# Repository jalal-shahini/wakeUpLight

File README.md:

# Wake up light

This is the circuit and code for a smart, super bight light that slowly brightens in the mornings to wake me up without an alarm.
The light can also be used as reading light at night with a timer to turn off automatically.
It features a 2004 LCD and a rotary encoder for user input.
The encoder has a calibrated debounce circuit and a schmitt-trigger for the cleanest possible signal.

An LED driver is required alongside this circuit.
I have decided to use a ZK-SJ20 to protect the LED from over current.
Max. LED power is 50 watts.
A CR2032 battery is required for the RTC to keep the time when the power is disconnected.

## To Do

* Since the device is connected to the wall outlet, energy efficiency was not of the highest concern. However, in feauture iterations, I will replace the linear voltage regulator with a buck converter.

**Disclaimer: The design is not yet ready for production. Therefore, the bom and positions files are not accurate.**

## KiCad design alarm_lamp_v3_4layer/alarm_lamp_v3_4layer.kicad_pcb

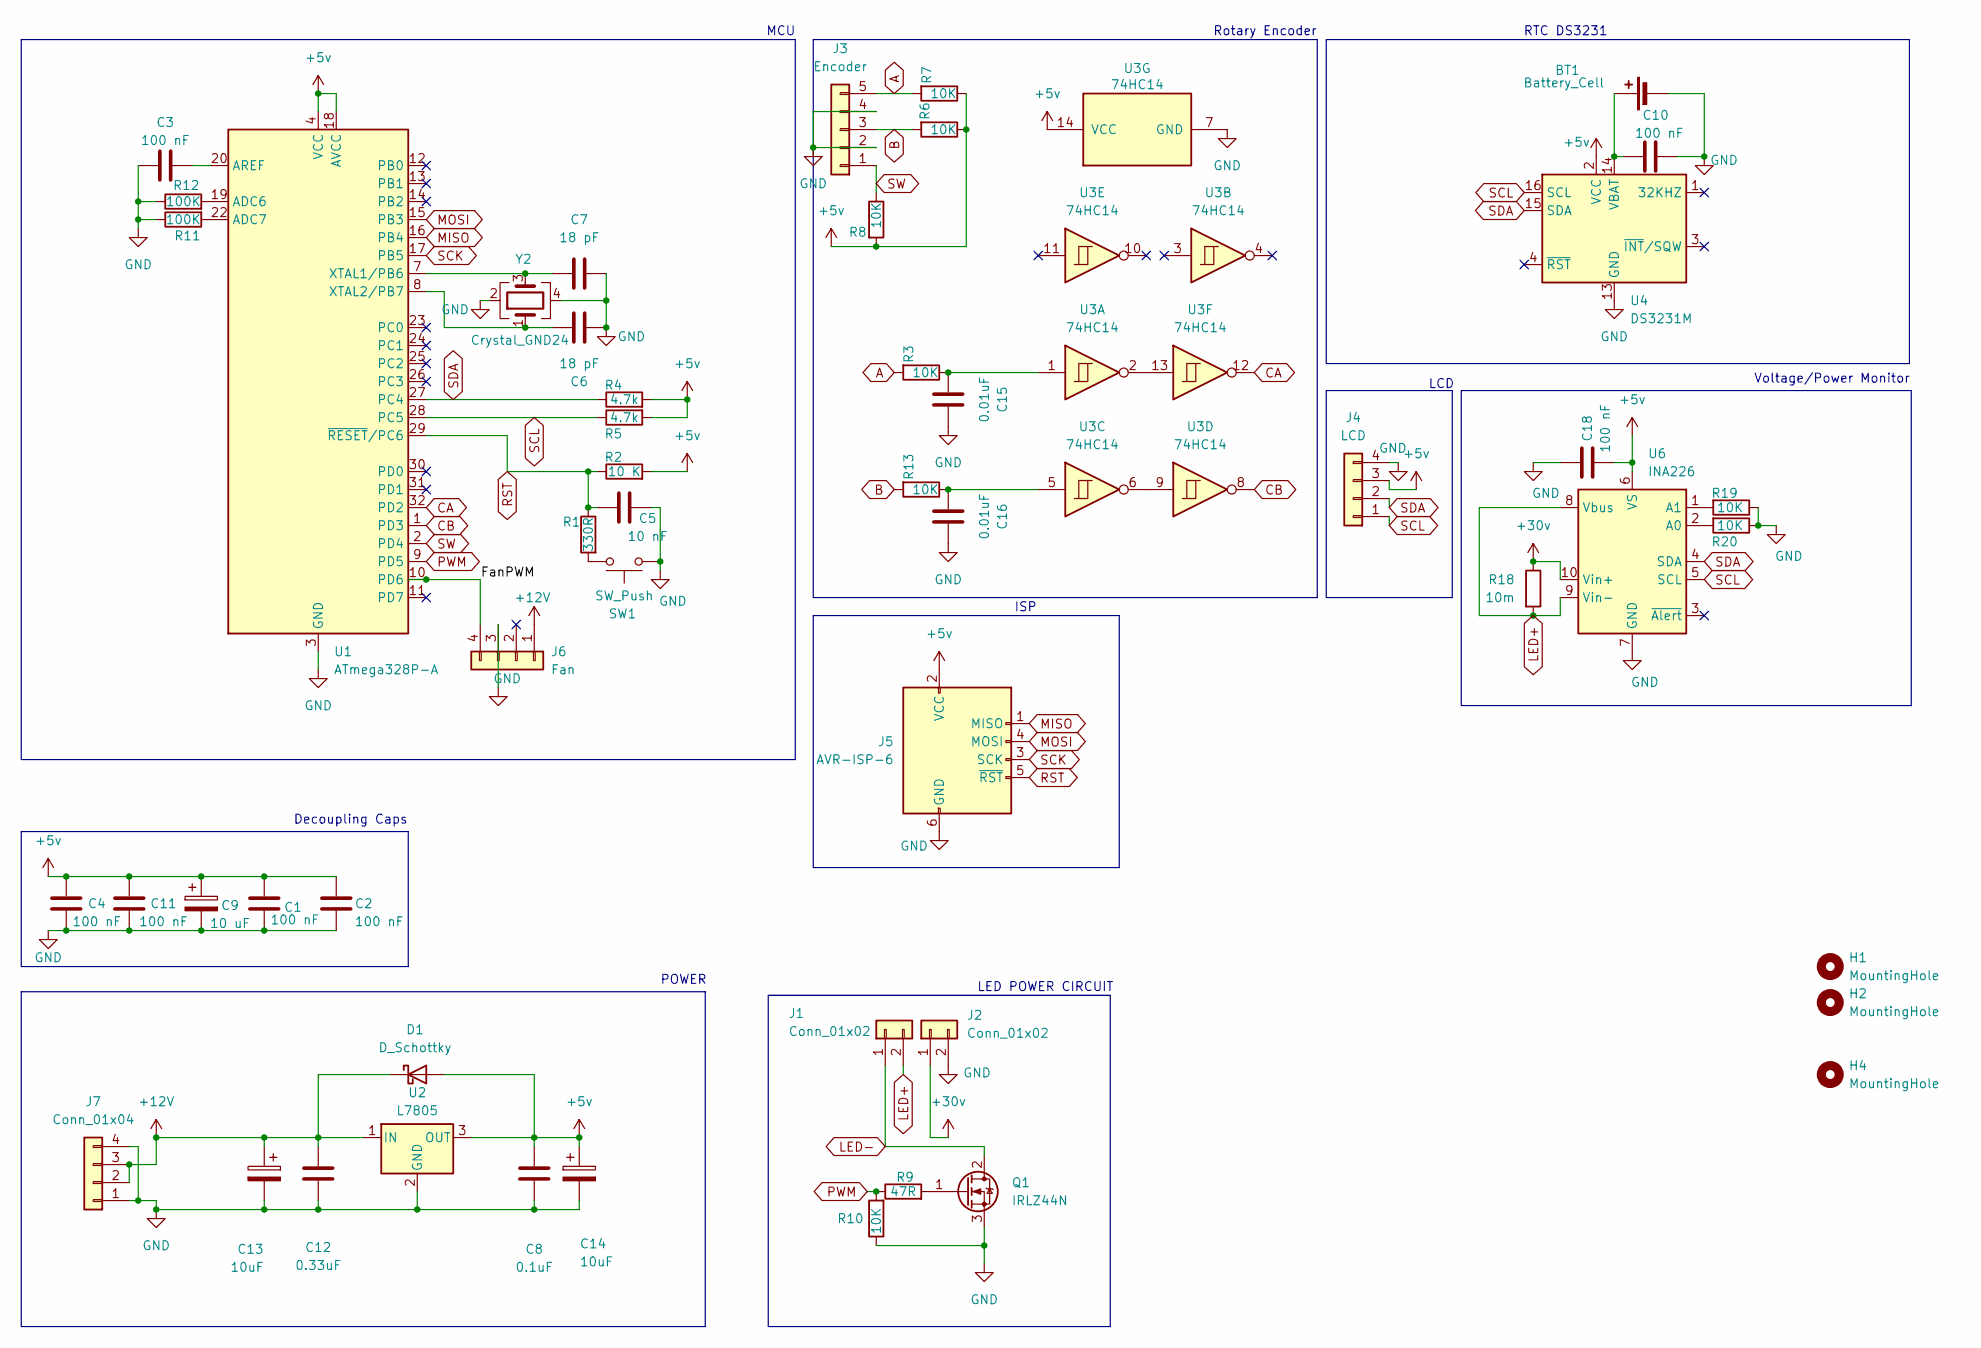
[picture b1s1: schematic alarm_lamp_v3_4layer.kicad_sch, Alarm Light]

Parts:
BT1: Battery_Cell; BatteryHolder_MYOUNG_BS-07-A1BJ001_CR2032; LCSC C5365915
C1, C4, C11, C18: 100 nF; C_0402_1005Metric; LCSC C1525
C2, C3: 100 nF; C_0603_1608Metric
C5: 10 nF; C_0603_1608Metric
C6, C7: 18 pF; C_0402_1005Metric; LCSC C1549
C8: 0.1uF; C_0603_1608Metric
C9: 10 uF; CP_Elec_4x5.3; LCSC C346925
C10: 100 nF; C_0402_1005Metric
C12: 0.33uF; C_0603_1608Metric
C13, C14: 10uF; CP_Elec_4x5.3; LCSC C346925
C15, C16: 0.01uF; C_0402_1005Metric
D1: D_Schottky; D_SOD-323; LCSC C191023
H1, H2, H4: MountingHole; MountingHole_3.2mm_M3
J1, J2: Conn_01x02; TerminalBlock_Phoenix_MKDS-1,5-2-5.08_1x02_P5.08mm_Horizont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
J3: Encoder; JST_XH_B5B-XH-A_1x05_P2.50mm_Vertical
J4: LCD; JST_XH_B4B-XH-A_1x04_P2.50mm_Vertical
J5: AVR-ISP-6; PinHeader_2x03_P2.54mm_Vertical
J6: Fan; JST_XH_B4B-XH-A_1x04_P2.50mm_Vertical
J7: Conn_01x04; TerminalBlock_Phoenix_MKDS-1,5-4-5.08_1x04_P5.08mm_Horizont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
Q1: IRLZ44N; TO-263-2; LCSC C19188232
R1: 330R; R_0603_1608Metric; LCSC C23138
R2: 10 K; R_0603_1608Metric; LCSC C17414
R3, R13: 10K; R_0402_1005Metric; LCSC C17414
R4, R5: 4.7k; R_0603_1608Metric
R6, R7, R8, R10: 10K; R_0603_1608Metric; LCSC C17414
R9: 47R; R_0603_1608Metric
R11, R12: 100K; R_0603_1608Metric; LCSC C25803
R18: 10m; R_2512_6332Metric
R19, R20: 10K; R_0603_1608Metric; LCSC C25804
SW1: SW_Push; SW_Push_1P1T_XKB_TS-1187A; LCSC C318884
U1: ATmega328P-A; TQFP-32_7x7mm_P0.8mm; LCSC C14877
U2: L7805; TO-263-2; LCSC C15077
U3: 74HC14; SOIC-14_3.9x8.7mm_P1.27mm; LCSC C5605
U4: DS3231M; SOIC-16W_7.5x10.3mm_P1.27mm; LCSC C9866
U6: INA226; VSSOP-10_3x3mm_P0.5mm; LCSC C2653835
Y2: Crystal_GND24; Crystal_SMD_3225-4Pin_3.2x2.5mm; LCSC C13738

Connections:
+5v: C1.1, C2.1, C4.1, C8.1, C9.1, C11.1, C14.1, C18.2, D1.2 (A), J4.3, J5.2 (VCC), R2.2, R4.2, R5.2, R6.1, R7.1, R8.2, U1.4 (VCC), U1.6 (VCC), U1.18 (AVCC), U2.3 (OUT), U3.14 (VCC), U4.2 (VCC), U6.6 (VS)
+12V: C12.1, C13.1, D1.1 (K), J6.1, J7.2, J7.3, U2.1 (IN)
+30v: J2.1, R18.1, U6.10 (Vin+)
/FanPWM: J6.4, U1.10 (PD6)
A: J3.5, R3.2, R7.2
B: J3.3, R6.2, R13.2
CA: U1.32 (PD2), U3.12
CB: U1.1 (PD3), U3.8
GND: BT1.2 (-), C1.2, C2.2, C3.2, C4.2, C5.2, C6.1, C7.1, C8.2, C9.2, C10.2, C11.2, C12.2, C13.2, C14.2, C15.1, C16.1, C18.1, J2.2, J3.2, J3.4, J4.4, J5.6 (GND), J6.3, J7.1, J7.4, Q1.3 (S), R10.1, R11.1, R12.1, R19.1, R20.1, SW1.2, U1.3 (GND), U1.5 (GND), U1.21 (GND), U2.2 (GND), U3.7 (GND), U4.5 (GND), U4.6 (GND), U4.7 (GND), U4.8 (GND), U4.9 (GND), U4.10 (GND), U4.11 (GND), U4.12 (GND), U4.13 (GND), U6.7 (GND), Y2.2, Y2.4
LED+: J1.2, R18.2, U6.8 (Vbus), U6.9 (Vin-)
LED-: J1.1, Q1.2 (D)
MISO: J5.1 (MISO), U1.16 (PB4)
MOSI: J5.4 (MOSI), U1.15 (PB3)
unnamed: BT1.1 (+), C10.1, U4.14 (VBAT)
unnamed: C15.2, R3.1, U3.1
unnamed: C16.2, R13.1, U3.5
unnamed: Q1.1 (G), R9.2
unnamed: R1.2, SW1.1
unnamed: R12.2, U1.19 (ADC6)
unnamed: R11.2, U1.22 (ADC7)
unnamed: C3.1, U1.20 (AREF)
unnamed: C7.2, U1.7 (XTAL1/PB6), Y2.3
unnamed: C6.2, U1.8 (XTAL2/PB7), Y2.1
unnamed: U3.6, U3.9
unnamed: U3.2, U3.13
unnamed: R20.2, U6.2 (A0)
unnamed: R19.2, U6.1 (A1)
PWM: R9.1, R10.2, U1.9 (PD5)
RST: C5.1, J5.5 (~RST), R1.1, R2.1, U1.29 (~RESET/PC6)
SCK: J5.3 (SCK), U1.17 (PB5)
SCL: J4.1, R5.1, U1.28 (PC5), U4.16 (SCL), U6.5 (SCL)
SDA: J4.2, R4.1, U1.27 (PC4), U4.15 (SDA), U6.4 (SDA)
SW: J3.1, R8.1, U1.2 (PD4)

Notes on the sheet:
POWER
LED POWER CIRCUIT
Rotary Encoder
LCD
RTC DS3231
Voltage/Power Monitor
ISP
Decoupling Caps
MCU

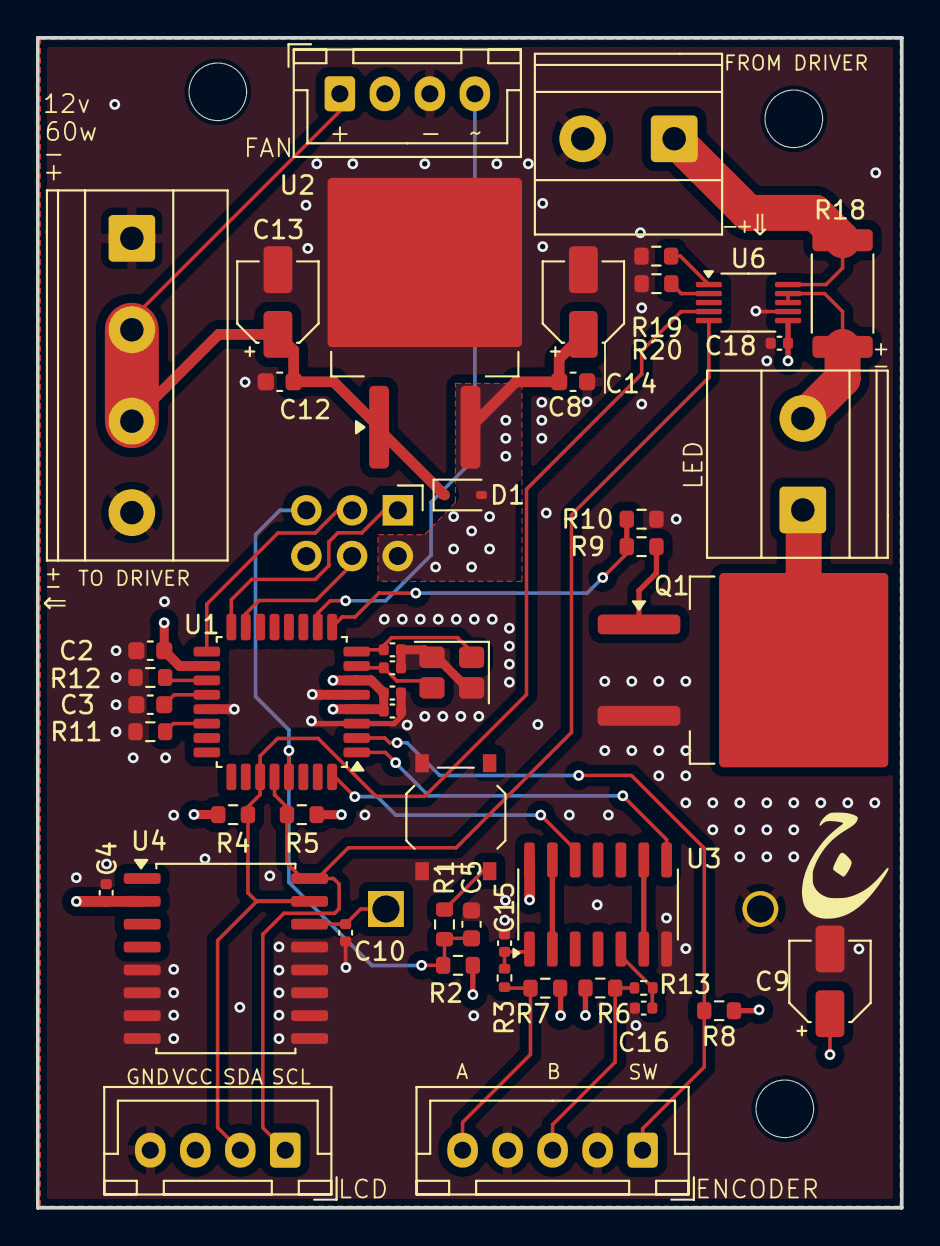
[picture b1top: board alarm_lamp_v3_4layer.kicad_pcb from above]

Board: 4 copper layers, 48.0 x 65.0 mm, 53 parts (1 on the bottom side), 33 nets.

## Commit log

2025-11-07 initial commit version 3
2025-11-08 readme file updated
2025-11-08 disclaimer added
